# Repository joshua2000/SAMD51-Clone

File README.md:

# SAMD51-Clone
Sparksfun SAMD51 clone. NOT MADE WITH LOVE

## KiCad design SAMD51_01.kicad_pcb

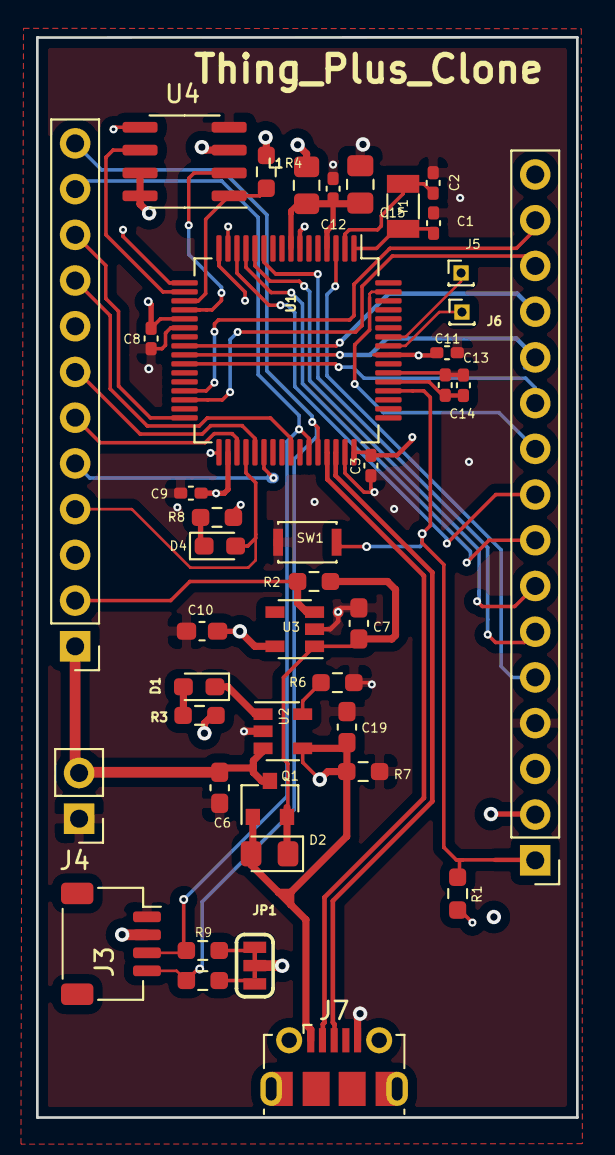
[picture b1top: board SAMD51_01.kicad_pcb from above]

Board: 4 copper layers, 30.0 x 60.0 mm, 42 parts (0 on the bottom side), 46 nets.

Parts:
C1, C2: 15pf; C_0402_1005Metric_Pad0.74x0.62mm_HandSolder
C3, C8, C9, C11, C12, C13, C14: 0.1uF; C_0402_1005Metric_Pad0.74x0.62mm_HandSolder
C6, C19: 4.7uF; C_0603_1608Metric_Pad1.08x0.95mm_HandSolder
C7: 1.0uF; C_0603_1608Metric_Pad1.08x0.95mm_HandSolder
C10: 2.2uF; C_0603_1608Metric_Pad1.08x0.95mm_HandSolder
C15: 10uF; C_0805_2012Metric_Pad1.18x1.45mm_HandSolder
D1: Red; LED_0603_1608Metric_Pad1.05x0.95mm_HandSolder
D2: 23V; D_0805_2012Metric_Pad1.15x1.40mm_HandSolder
D4: GREEN; LED_0603_1608Metric_Pad1.05x0.95mm_HandSolder
J1: Conn_01x12_Male; PinHeader_1x12_P2.54mm_Vertical
J2: Conn_01x16_Male; PinHeader_1x16_P2.54mm_Vertical
J3: Conn_01x04_Male; JST_SH_SM04B-SRSS-TB_1x04-1MP_P1.00mm_Horizontal
J4: Conn_01x02_Male; PinHeader_1x02_P2.54mm_Vertical
J5, J6: Conn_01x01; PinHeader_1x01_P1.00mm_Vertical
J7: USB_B_Micro; USB_Micro-B_Molex-105017-0001
JP1: SolderJumper_3_Open; SMT-JUMPER_3_2-NC_TRACE_SILK
L1: 300ohm; L_0805_2012Metric_Pad1.15x1.40mm_HandSolder
Q1: 30V; SOT-23
R1, R4: 10K; R_0603_1608Metric_Pad0.98x0.95mm_HandSolder
R2, R7: 10k; R_0603_1608Metric_Pad0.98x0.95mm_HandSolder
R3: 1K; R_0603_1608Metric_Pad0.98x0.95mm_HandSolder
R5, R9: 2.2k; R_0603_1608Metric_Pad0.98x0.95mm_HandSolder
R6: 2K; R_0603_1608Metric_Pad0.98x0.95mm_HandSolder
R8: 330ohms; R_0603_1608Metric_Pad0.98x0.95mm_HandSolder
SW1: SW_Push; SW_SPST_CK_KXT3
U1: ATSAMD51J20A-A; TQFP-64_10x10mm_P0.5mm
U2: MCP73831-2-OT; SOT-23-5
U3: AP2112K-3.3; SOT-23-5
U4: 4Mb Flash; SOIC-8_3.9x4.9mm_P1.27mm
Y1: 32.768KHz; Crystal_SMD_3215-2Pin_3.2x1.5mm

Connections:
+3V3: C3.1, C8.1, C9.1, C10.1, C11.1, J2.2, J3.2, JP1.2, L1.1, R1.1, R4.2, U1.21, U1.34, U1.48, U1.56, U3.5, U4.3, U4.7, U4.8
/A0: J2.5, U1.3
/A1: J2.6, U1.11
/A2: J2.7, U1.12
/A3: J2.8, U1.13
/A4: J2.9, U1.14
/A5: J2.10, U1.63
/D0: J2.14, U1.30
/D1: J2.15, U1.29
/D4: J2.16, U1.15
/D5: J1.10, U1.32
/D6: J1.9, U1.41
/D9: J1.8, U1.16
/D10: J1.7, U1.37
/D11: J1.6, U1.35
/D12: J1.5, U1.38
/FLASH_CS: R4.1, U1.19, U4.1
/FLASH_MISO: U1.20, U4.2
/FLASH_MOSI: U1.17, U4.5
/FLASH_SCK: U1.18, U4.6
/XIN32: C1.1, U1.1, Y1.1
/XOUT32: C2.1, U1.2, Y1.2
D13: D4.2, J1.4, U1.36
D+: J7.3, U1.46
D-: J7.2, U1.45
EN: J1.2, R2.1, U3.3
GND: C1.2, C2.2, C3.2, C6.2, C7.2, C8.2, C9.2, C10.2, C11.2, C12.2, C13.2, C14.2, C15.2, C19.2, J2.4, J3.1, J4.1, J7.5, R6.2, R7.2, R8.2, SW1.1, U1.7, U1.22, U1.33, U1.47, U1.54, U2.2, U3.2, U4.4
MISO: J2.13, U1.24
MOSI: J2.12, U1.25
unnamed: D1.1, U2.1
unnamed: D1.2, R3.1
unnamed: D4.1, R8.1
unnamed: JP1.1, R5.2
unnamed: JP1.3, R9.2
unnamed: R6.1, U2.5
RESET: J2.1, R1.2, SW1.2, U1.52
SCK: J2.11, U1.26
SCL: J1.12, J3.4, R5.1, U1.44
SDA: J1.11, J3.3, R9.1, U1.43
SWDCLK: J6.1, U1.57
SWDIO: J5.1, U1.58
VCC: C13.1, C14.1, U1.53
VDDA: C12.1, C15.1, L1.2, U1.4, U1.8
VIN: C7.1, D2.1, Q1.2, R2.2, U3.1
V_BATT: C6.1, J1.1, J4.2, Q1.3, U2.3
V_USB: C19.1, D2.2, J1.3, J7.1, Q1.1, R3.2, R7.1, U2.4

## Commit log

2021-06-22 clone
    Later add everything
